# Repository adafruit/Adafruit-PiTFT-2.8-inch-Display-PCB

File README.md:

# Adafruit PiTFT 2.8 inch LCD Display PCB
<a href="http://www.adafruit.com/products/1601"><br/>
Click here to purchase one from the Adafruit shop</a>

This display features a 2.8" LCD with 320x240 16-bit color pixels and a resistive touch overlay. The plate uses the high speed SPI interface on the Pi and can use the mini display as a console, X window port, displaying images or video etc. Best of all it plugs right in on top!

It's designed to fit nicely onto the Pi 1 Model A or B but also works OK with the Pi Zero, Pi 3, Pi 2 or Pi 1 Model A+ or B+ (any Pi with a 2x20 connector) as long as you don't mind the PCB overhangs the USB ports by 5mm, see the photos above. If you have a modern Pi with a 2x20 connector, you may want to grab a PiTFT 2.8" Plus which does not overhang

PCB files for Adafruit PiTFT 2.8 inch Resistive Touch Display. The format is EagleCAD schematic and board layout 
- https://www.adafruit.com/product/1601

### License

Adafruit invests time and resources providing this open source design, please support Adafruit and open-source hardware by purchasing products from [Adafruit](https://www.adafruit.com)!

All text above must be included in any redistribution

Designed by Limor Fried/Ladyada for Adafruit Industries.
Creative Commons Attribution/Share-Alike, all text above must be included in any redistribution. 
See license.txt for additional information.

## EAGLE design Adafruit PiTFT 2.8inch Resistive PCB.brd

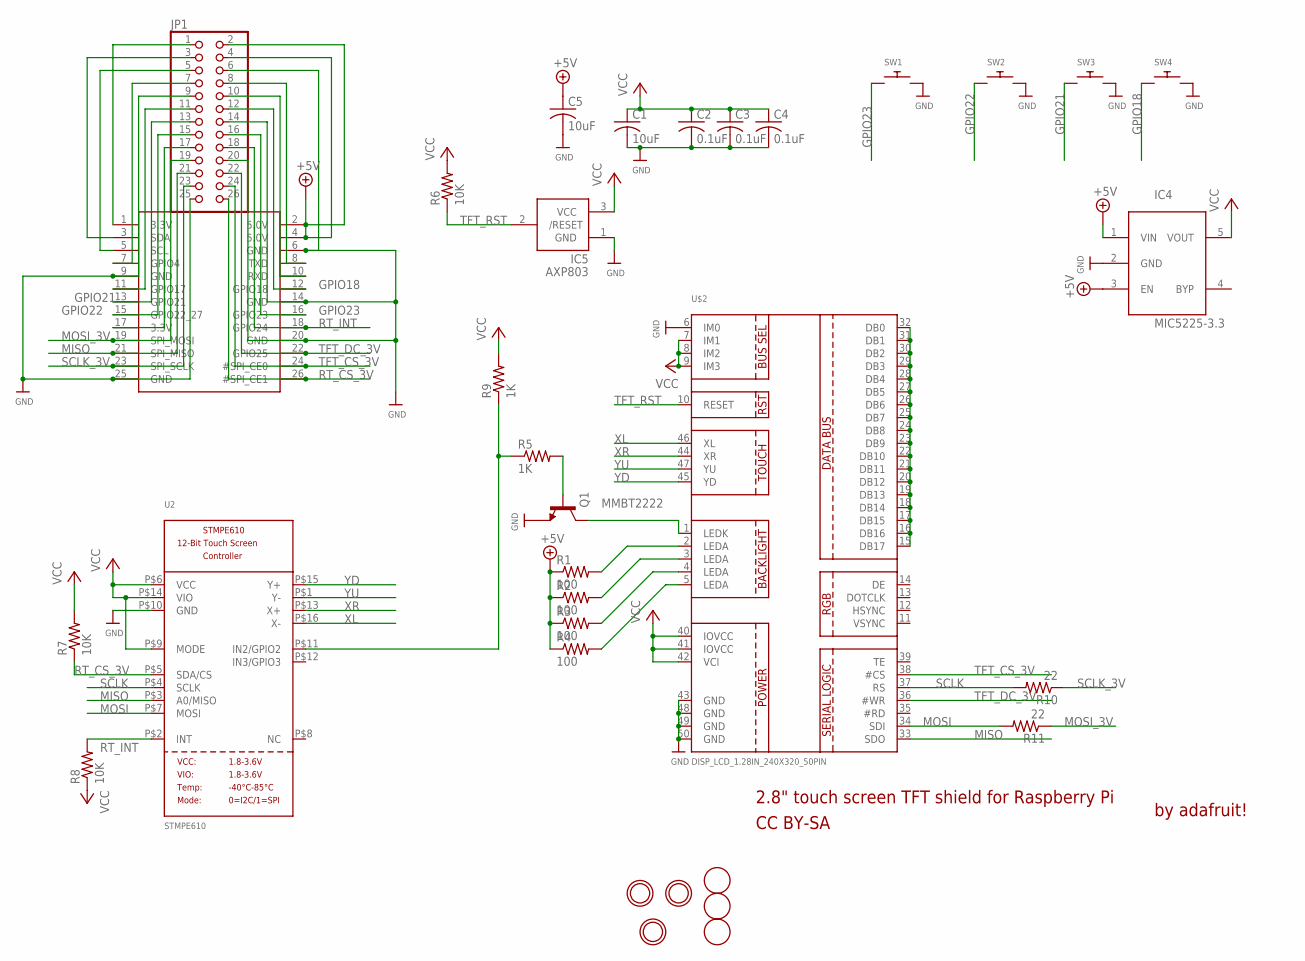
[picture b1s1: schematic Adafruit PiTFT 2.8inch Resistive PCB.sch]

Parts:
C1, C5: 10uF; C0805K
C2, C3, C4: 0.1uF; C0805K
IC4: MIC5225-3.3; SOT23-5L
IC5: AXP803; SOT23
JP1: HEADER-2X13; 2X13
Q1: MMBT2222; SOT23-BEC
R1, R2, R3, R4: 100; R0805
R5, R9: 1K; R0805
R6, R7, R8: 10K; R0805
R10, R11: 22; R0805
SW1, SW2, SW3, SW4: SWITCH_PUSHBUTTONEVQ-PE; TACT_PANA-EVQ
U2: STMPE610; QFN16_3MM
U$2: DISP_LCD_1.28IN_240X320_50PIN; TFT_2.83IN_240X320_50PIN
U$3: RASPBERRYPI_B_MODELB_V2; RASPBERRYPIV2_SHIELD
U$10, U$11, U$18: FIDUCIAL; FIDUCIAL_1MM
U$15, U$16, U$17: MOUNTINGHOLE2.5_THICK; MOUNTINGHOLE_2.5_PLATED_THICK

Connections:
3.3V: JP1.1, U$3.1 (3.3V)
3.3V@2: JP1.17, U$3.17 (3.3V)
+5V: C5.1, IC4.1 (VIN), IC4.3 (EN), JP1.2, JP1.4, R1.1, R2.1, R3.1, R4.1, U$3.2 (5.0V), U$3.4 (5.0V)
GND: C1.2, C2.2, C3.2, C4.2, C5.2, IC4.2 (GND), IC5.1 (GND), JP1.6, JP1.9, JP1.14, JP1.20, JP1.25, Q1.E, SW1.P$2, SW2.P$2, SW3.P$2, SW4.P$2, U2.P$10 (GND), U$2.6 (IM0), U$2.43 (GND), U$2.48 (GND), U$2.49 (GND), U$2.50 (GND), U$3.6 (GND), U$3.9 (GND), U$3.14 (GND), U$3.20 (GND), U$3.25 (GND)
GPIO18: JP1.12, SW4.P$1, U$3.12 (GPIO18)
GPIO21: JP1.13, SW3.P$1, U$3.13 (GPIO21)
GPIO22: JP1.15, SW2.P$1, U$3.15 (GPIO22_27)
GPIO23: JP1.16, SW1.P$1, U$3.16 (GPIO23)
MISO: JP1.21, U2.P$3 (A0/MISO), U$2.33 (SDO), U$3.21 (SPI_MISO)
MOSI: R11.2, U2.P$7 (MOSI), U$2.34 (SDI)
MOSI_3V: JP1.19, R11.1, U$3.19 (SPI_MOSI)
unnamed: Q1.C, U$2.1 (LEDK)
unnamed: R1.2, U$2.2 (LEDA)
unnamed: R2.2, U$2.3 (LEDA)
unnamed: R3.2, U$2.4 (LEDA)
unnamed: R5.1, R9.1, U2.P$11 (IN2/GPIO2)
unnamed: JP1.3, U$3.3 (SDA)
unnamed: JP1.5, U$3.5 (SCL)
unnamed: JP1.7, U$3.7 (GPIO4)
unnamed: U$2.15 (DB17), U$2.16 (DB16), U$2.17 (DB15), U$2.18 (DB14), U$2.19 (DB13), U$2.20 (DB12), U$2.21 (DB11), U$2.22 (DB10), U$2.23 (DB9), U$2.24 (DB8), U$2.25 (DB7), U$2.26 (DB6), U$2.27 (DB5), U$2.28 (DB4), U$2.29 (DB3), U$2.30 (DB2), U$2.31 (DB1), U$2.32 (DB0)
unnamed: R4.2, U$2.5 (LEDA)
unnamed: JP1.11, U$3.11 (GPIO17)
unnamed: Q1.B, R5.2
unnamed: JP1.10, U$3.10 (RXD)
unnamed: JP1.8, U$3.8 (TXD)
RT_CS_3V: JP1.26, R7.1, U2.P$5 (SDA/CS), U$3.26 (#SPI_CE1)
RT_INT: JP1.18, R8.2, U2.P$2 (INT), U$3.18 (GPIO24)
SCLK: R10.2, U2.P$4 (SCLK), U$2.37 (RS)
SCLK_3V: JP1.23, R10.1, U$3.23 (SPI_SCLK)
TFT_CS_3V: JP1.24, U$2.38 (#CS), U$3.24 (#SPI_CE0)
TFT_DC_3V: JP1.22, U$2.36 (#WR), U$3.22 (GPIO25)
TFT_RST: IC5.2 (/RESET), R6.1, U$2.10 (RESET)
VCC: C1.1, C2.1, C3.1, C4.1, IC4.5 (VOUT), IC5.3 (VCC), R6.2, R7.2, R8.1, R9.2, U2.P$6 (VCC), U2.P$9 (MODE), U2.P$14 (VIO), U$2.7 (IM1), U$2.8 (IM2), U$2.9 (IM3), U$2.40 (IOVCC), U$2.41 (IOVCC), U$2.42 (VCI)
XL: U2.P$16 (X-), U$2.46 (XL)
XR: U2.P$13 (X+), U$2.44 (XR)
YD: U2.P$15 (Y+), U$2.45 (YD)
YU: U2.P$1 (Y-), U$2.47 (YU)

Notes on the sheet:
2.8" touch screen TFT shield for Raspberry Pi
by adafruit!
CC BY-SA

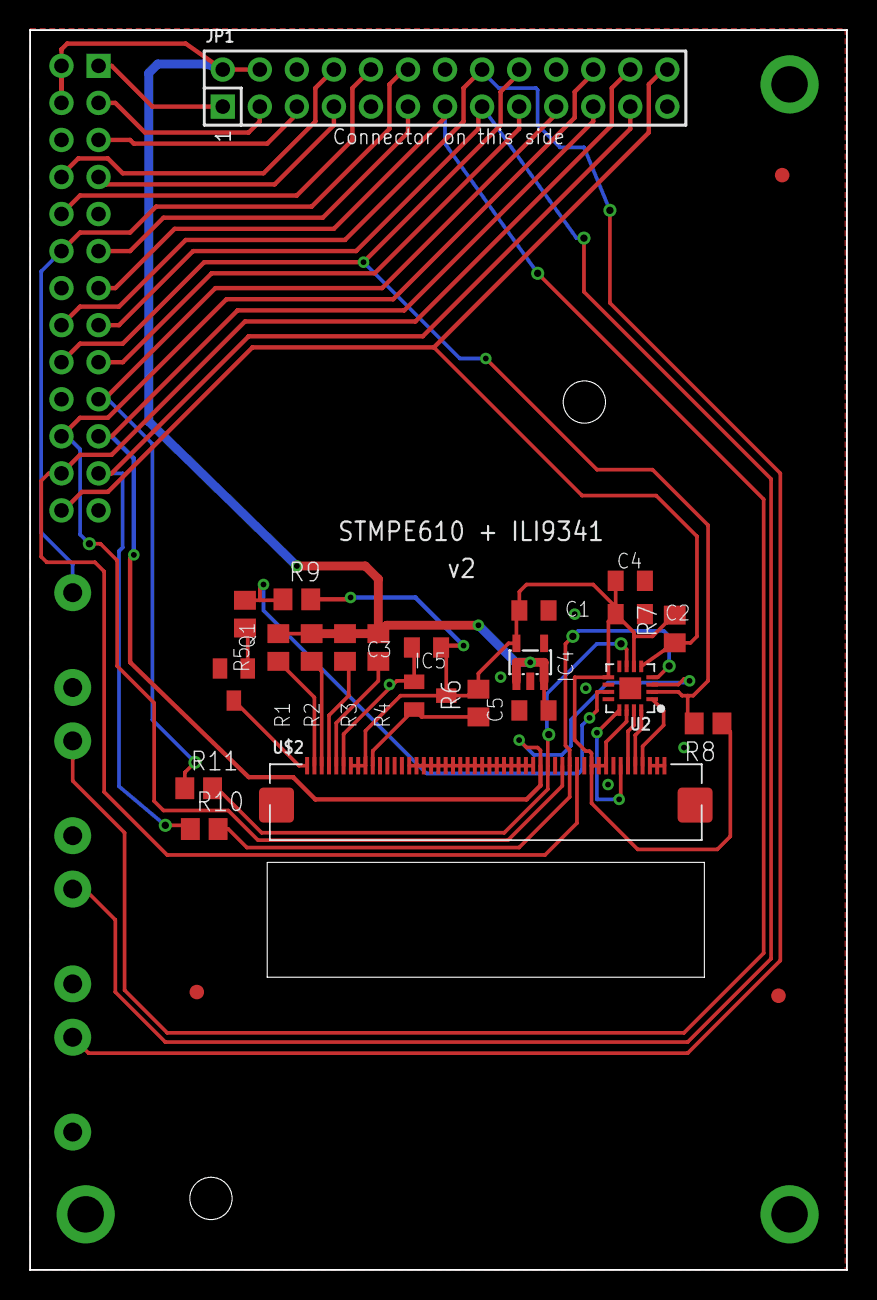
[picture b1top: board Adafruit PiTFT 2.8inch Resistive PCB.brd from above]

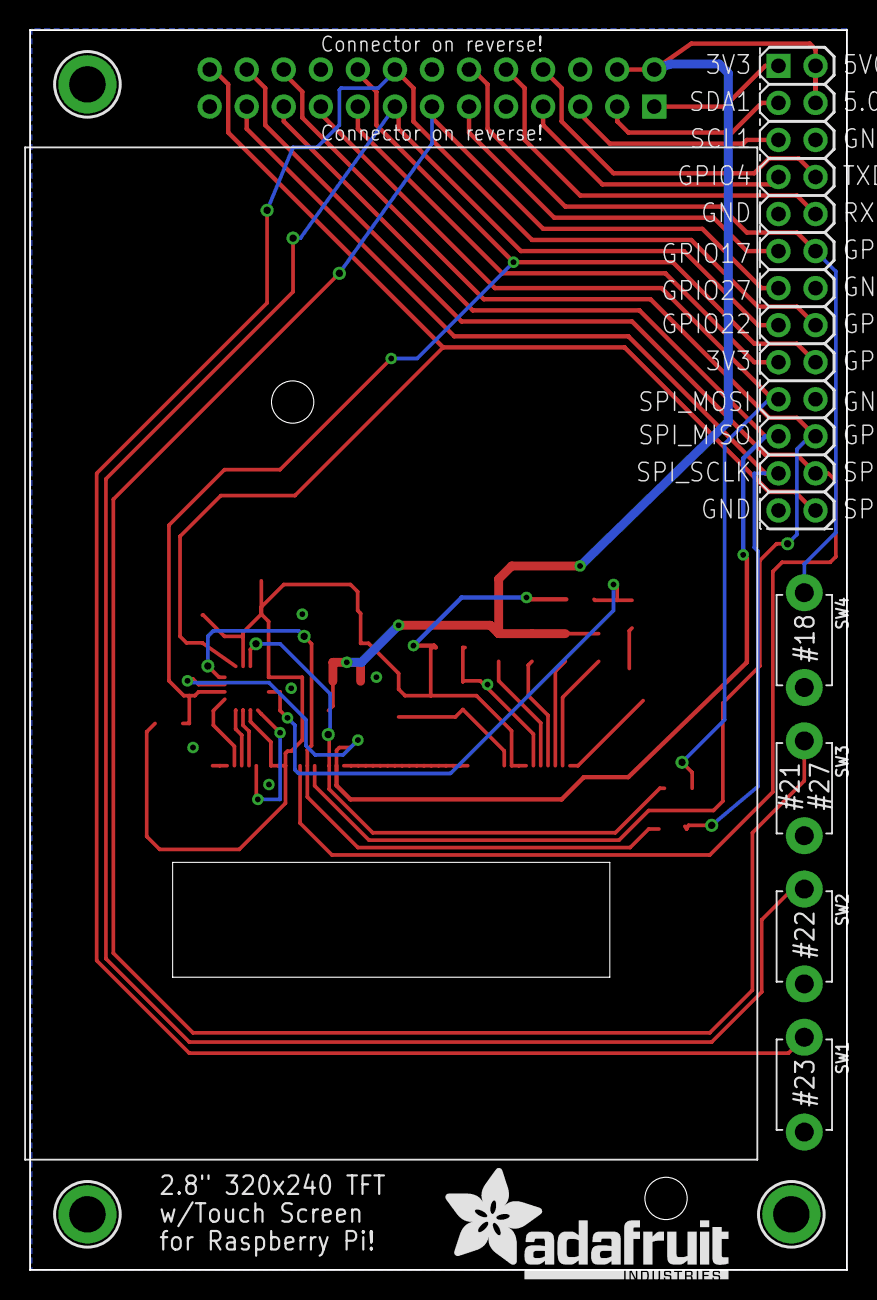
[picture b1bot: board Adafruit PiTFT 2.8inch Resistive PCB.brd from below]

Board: 2 copper layers, 56.0 x 85.0 mm, 34 parts (10 on the bottom side), 37 nets.

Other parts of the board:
U$23: ADAFRUIT_TEXT_20MM

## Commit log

2015-03-08 init
2015-03-08 add url
